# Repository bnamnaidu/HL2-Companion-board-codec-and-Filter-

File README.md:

# HL2-Companion-board-codec-and-Filter-

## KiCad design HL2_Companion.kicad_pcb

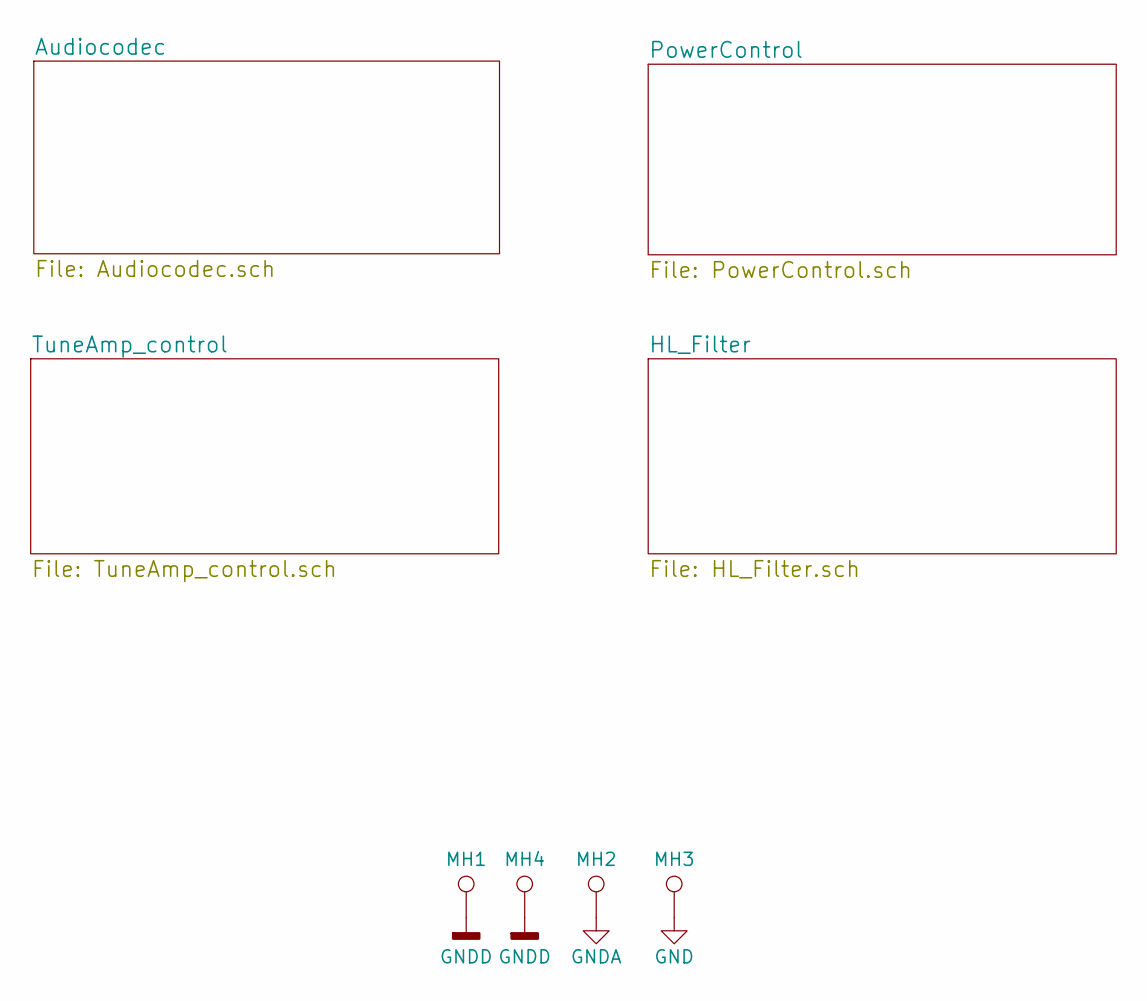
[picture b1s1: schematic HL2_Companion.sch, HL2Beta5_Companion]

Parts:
MH1, MH2, MH3, MH4: TEST_1P; m3

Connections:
GND: MH3.1; also elsewhere on the board
GNDA: MH2.1; also elsewhere on the board
GNDD: MH1.1, MH4.1; also elsewhere on the board

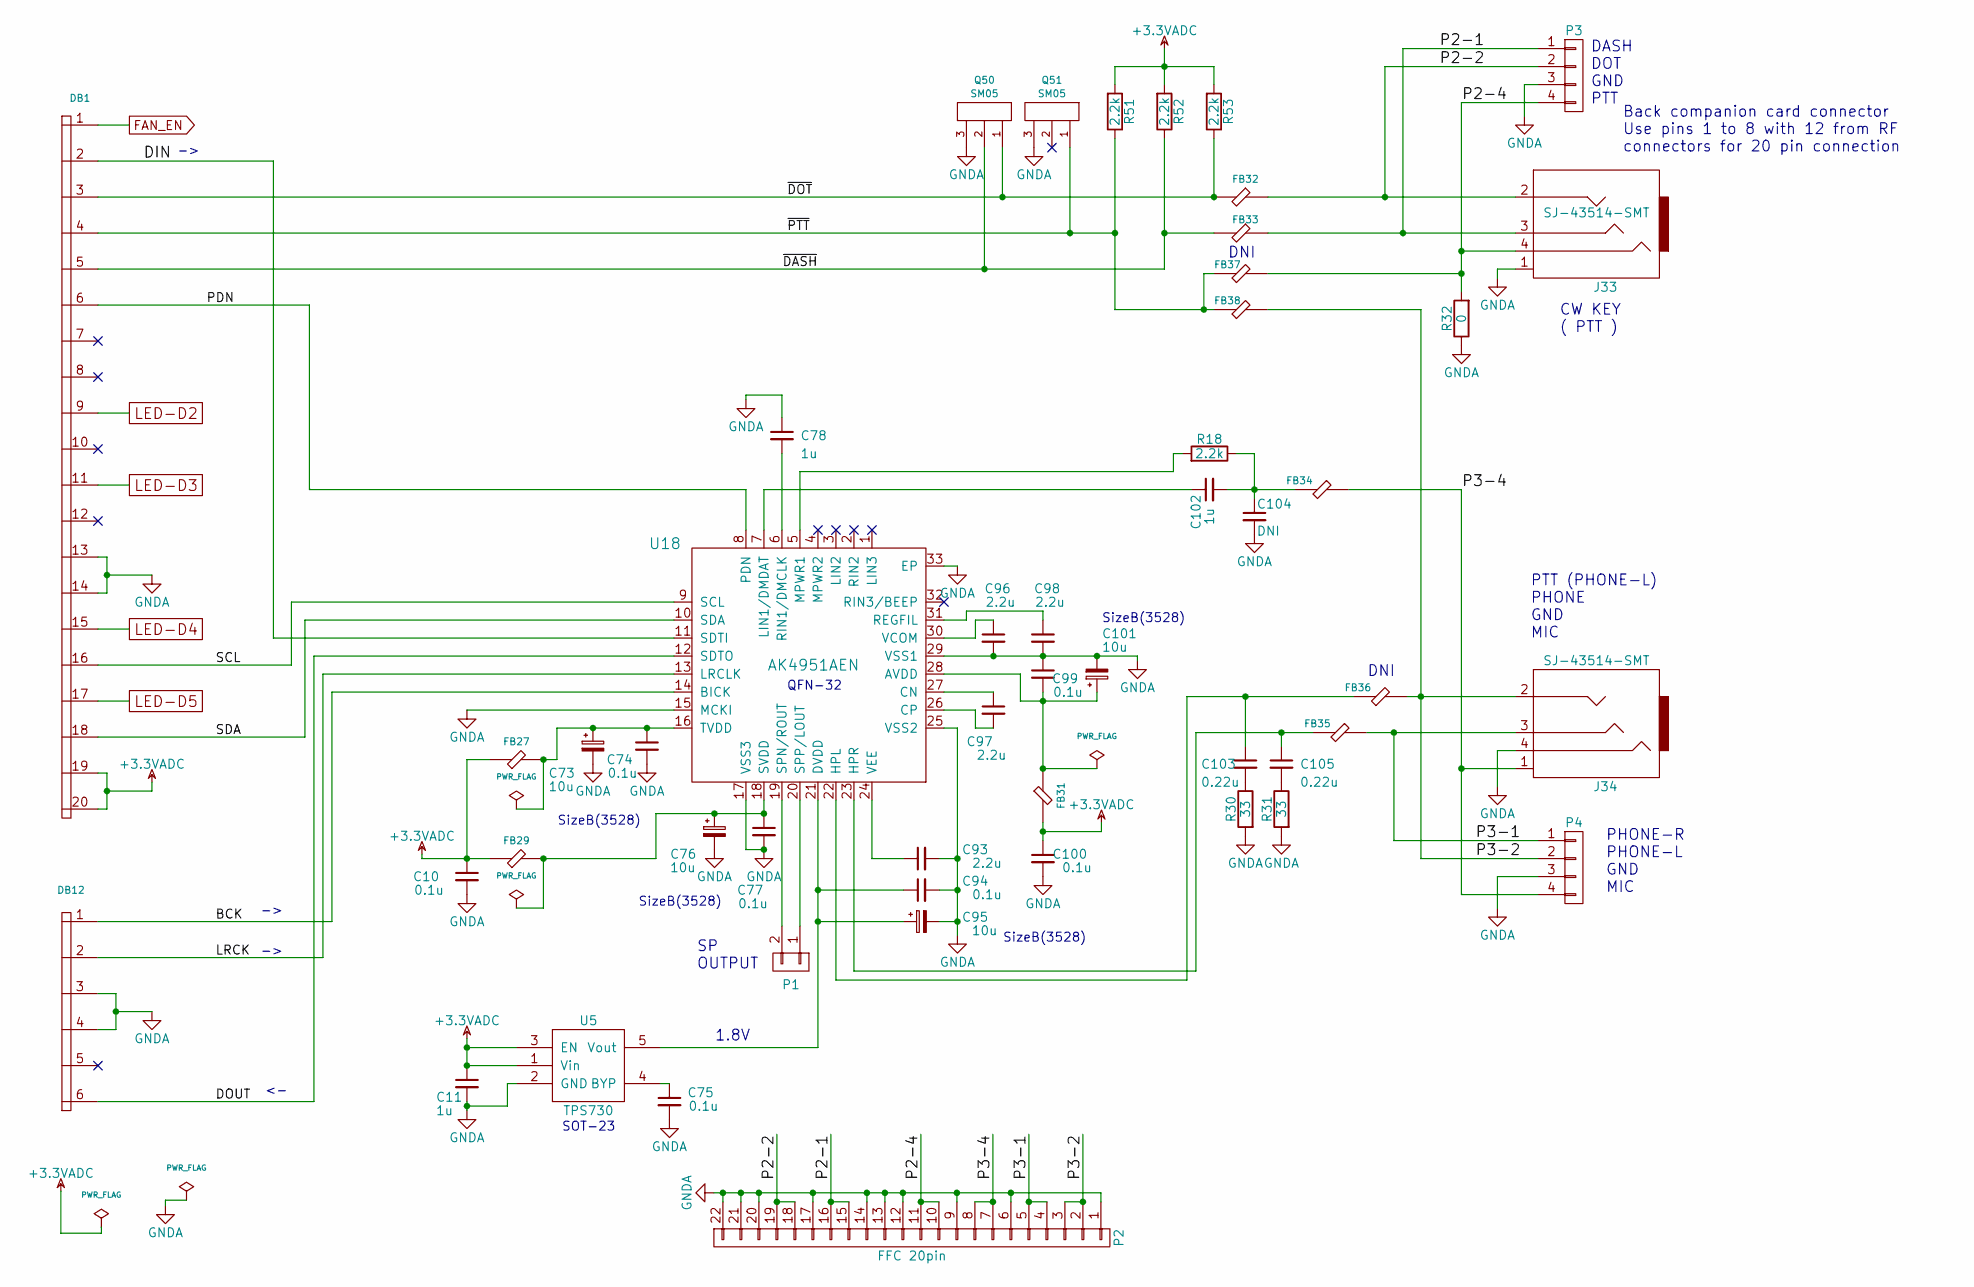
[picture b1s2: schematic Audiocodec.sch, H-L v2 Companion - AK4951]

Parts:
C10, C74, C75, C77, C94, C99, C100: 0.1u; C_0603_HandSoldering
C11, C78, C102: 1u; C_0603_HandSoldering
C73, C76, C95, C101: 10u; TantalC_SizeB_EIA-3528_Wave
C93, C96, C97, C98: 2.2u; C_0603_HandSoldering
C103, C105: 0.22u; C_0603_HandSoldering
C104: DNI; C_0603_HandSoldering
DB1: IO20; 10x2
DB12: IO6b; 3x2
FB27, FB29, FB31, FB32, FB33, FB34, FB35, FB36, FB37, FB38: FB; C_0603_HandSoldering
J33, J34: SJ-43514-SMT
P1: CONN_01X02; Pin_Header_Straight_1x02_Pitch2.54mm
P2: FFC 20pin; FFC_Kyocera_20pin
P3, P4: CONN_01X04; Pin_Header_Straight_1x04_Pitch2.54mm
Q50, Q51: SM05; SOT-23
R18, R51, R52, R53: 2.2k; C_0603_HandSoldering
R30, R31: 33; C_0603_HandSoldering
R32: 0; C_0603_HandSoldering
U5: TPS730; SOT23
U18: AK4951AEN; QFN-32-1EP_4x4mm_Pitch0.4mm_Handsoldering

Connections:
+3.3VADC: C10.1, C11.1, C100.1, DB1.19, DB1.20, FB27.2, FB29.2, FB31.1, R51.2, R52.2, R53.2, U5.1 (Vin), U5.3 (EN)
/Audiocodec/BCK: DB12.1, U18.14 (BICK)
/Audiocodec/DIN: DB1.2, U18.11 (SDTI)
/Audiocodec/DOUT: DB12.6, U18.12 (SDTO)
/Audiocodec/LRCK: DB12.2, U18.13 (LRCLK)
/Audiocodec/P2-1: FB33.2, J33.3, P2.15, P2.16, P3.1
/Audiocodec/P2-2: FB32.2, J33.2, P2.18, P2.19, P3.2
/Audiocodec/P2-4: FB37.1, J33.4, P2.10, P2.11, P3.4, R32.2
/Audiocodec/P3-1: FB35.2, J34.3, P2.4, P2.5, P4.1
/Audiocodec/P3-2: FB36.1, FB38.1, J34.2, P2.2, P2.3, P4.2
/Audiocodec/P3-4: FB34.2, J34.1, P2.7, P2.8, P4.4
/Audiocodec/PDN: DB1.6, U18.8 (PDN)
/Audiocodec/SCL: DB1.16, U18.9 (SCL)
/Audiocodec/SDA: DB1.18, U18.10 (SDA)
/Audiocodec/~DASH: DB1.5, FB33.1, Q50.2, R52.1
/Audiocodec/~DOT: DB1.3, FB32.1, Q50.1, R53.1
/Audiocodec/~PTT: DB1.4, FB37.2, FB38.2, Q51.1, R51.1
FAN_EN: DB1.1; also elsewhere on the board
GNDA: C10.2, C11.2, C73.2, C74.2, C75.2, C76.2, C77.2, C78.1, C93.2, C94.2, C95.2, C96.2, C98.2, C99.1, C100.2, C101.2, C104.2, DB1.13, DB1.14, DB12.3, DB12.4, J33.1, J34.4, P2.1, P2.6, P2.9, P2.12, P2.13, P2.14, P2.17, P2.20, P2.21, P2.22, P3.3, P4.3, Q50.3, Q51.3, R30.2, R31.2, R32.1, U5.2 (GND), U18.15 (MCKI), U18.17 (VSS3), U18.25 (VSS2), U18.29 (VSS1), U18.33 (EP); also elsewhere on the board
LED-D2: DB1.9; also elsewhere on the board
LED-D3: DB1.11; also elsewhere on the board
LED-D4: DB1.15; also elsewhere on the board
LED-D5: DB1.17; also elsewhere on the board
unnamed: C73.1, C74.1, FB27.1, U18.16 (TVDD)
unnamed: C75.1, U5.4 (BYP)
unnamed: C76.1, C77.1, FB29.1, U18.18 (SVDD)
unnamed: C78.2, U18.6 (RIN1/DMCLK)
unnamed: C93.1, U18.24 (VEE)
unnamed: C94.1, C95.1, U5.5 (Vout), U18.21 (DVDD)
unnamed: C96.1, U18.30 (VCOM)
unnamed: C97.1, U18.27 (CN)
unnamed: C97.2, U18.26 (CP)
unnamed: C98.1, U18.31 (REGFIL)
unnamed: C99.2, C101.1, FB31.2, U18.28 (AVDD)
unnamed: C102.1, U18.7 (LIN1/DMDAT)
unnamed: C102.2, C104.1, FB34.1, R18.1
unnamed: C103.1, FB36.2, U18.22 (HPL)
unnamed: C103.2, R30.1
unnamed: C105.1, FB35.1, U18.23 (HPR)
unnamed: C105.2, R31.1
unnamed: P1.1, U18.20 (SPP/LOUT)
unnamed: P1.2, U18.19 (SPN/ROUT)
unnamed: R18.2, U18.5 (MPWR1)

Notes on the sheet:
Back companion card connector Use pins 1 to 8 with 12 from RF connectors for 20 pin connection
SP OUTPUT
CW KEY ( PTT )
PTT (PHONE-L) PHONE GND MIC
1.8V
DNI
PHONE-R PHONE-L GND MIC
DASH DOT GND PTT
SizeB(3528)
SOT-23
QFN-32

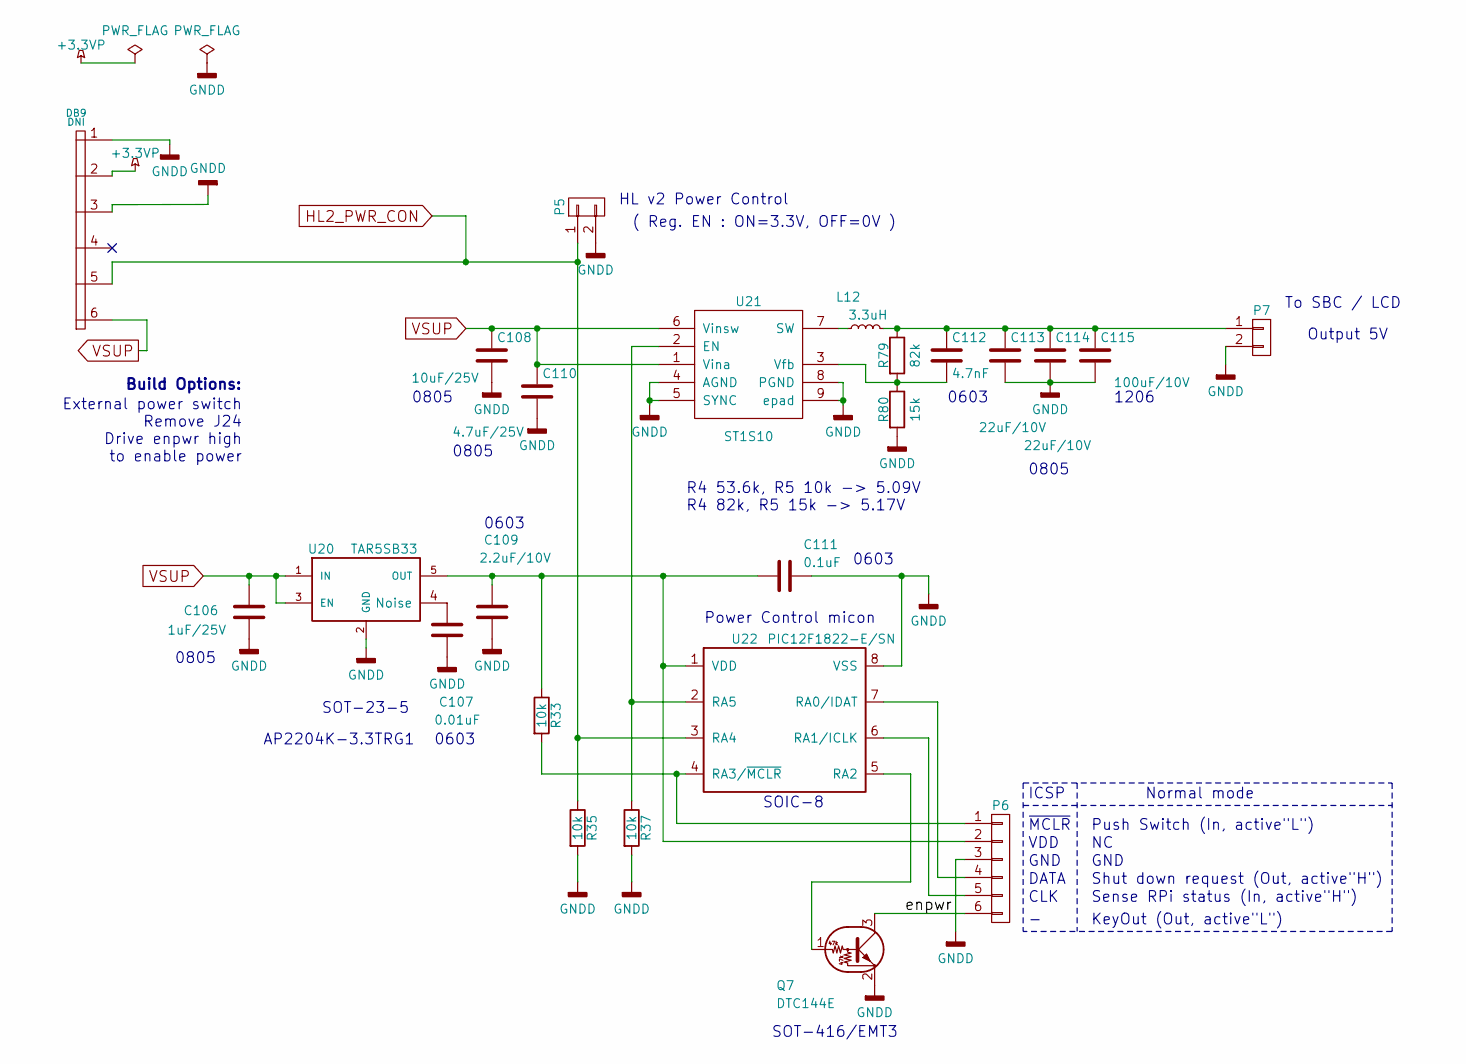
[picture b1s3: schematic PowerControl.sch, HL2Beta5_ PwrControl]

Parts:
C106: 1uF/25V; SMD-0805
C107: 0.01uF; SMD-0603
C108: 10uF/25V; SMD-0805
C109: 2.2uF/10V; SMD-0603
C110: 4.7uF/25V; SMD-0805
C111: 0.1uF; SMD-0603
C112: 4.7nF; SMD-0603
C113, C114: 22uF/10V; SMD-0805
C115: 100uF/10V; SMD-1206
DB9: IO6b; 6x1
L12: 3.3uH; GENERICPSL
P5: CONN_01X02; Pin_Header_Straight_1x02_Pitch2.54mm
P6: CONN_01X06; Pin_Header_Straight_1x06_Pitch2.54mm
P7: CONN_01X02; PINHEAD1-2
Q7: DTC144E; SOT416
R33, R35, R37: 10k; SMD-0603
R79: 82k; SMD-0603
R80: 15k; SMD-0603
U20: TAR5SB33; SOT-23-5
U21: ST1S10
U22: PIC12F1822-E/SN; SOIC-8_3.9x4.9mm_Pitch1.27mm

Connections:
+3.3VP: DB9.2; also elsewhere on the board
/PowerControl/enpwr: P6.6, Q7.3 (C)
GNDD: C106.2, C107.2, C108.2, C109.2, C110.2, C111.1, C113.2, C114.2, C115.2, DB9.1, DB9.3, P5.2, P6.3, P7.2, Q7.2 (E), R35.2, R37.2, R80.2, U20.2 (GND), U21.4 (AGND), U21.5 (SYNC), U21.8 (PGND), U21.9 (epad), U22.8 (VSS); also elsewhere on the board
HL2_PWR_CON: DB9.5, P5.1, R35.1, U22.3 (RA4); also elsewhere on the board
unnamed: C107.1, U20.4 (Noise)
unnamed: C109.1, C111.2, P6.2, R33.1, U20.5 (OUT), U22.1 (VDD)
unnamed: C112.1, C113.1, C114.1, C115.1, L12.1, P7.1, R79.1
unnamed: C112.2, R79.2, R80.1, U21.3 (Vfb)
unnamed: L12.2, U21.7 (SW)
unnamed: P6.1, R33.2, U22.4 (RA3/~MCLR)
unnamed: P6.4, U22.7 (RA0/IDAT)
unnamed: P6.5, U22.6 (RA1/ICLK)
unnamed: Q7.1 (B), U22.5 (RA2)
unnamed: R37.1, U21.2 (EN), U22.2 (RA5)
VSUP: C106.1, C108.1, C110.1, DB9.6, U20.1 (IN), U20.3 (EN), U21.1 (Vina), U21.6 (Vinsw); also elsewhere on the board

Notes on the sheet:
To SBC / LCD
ICSP
~MCLR
VDD
GND
DATA
CLK
Shut down request (Out, active"H")
Sense RPi status (In, active"H")
Output 5V
Normal mode
Push Switch (In, active"L")
HL v2 Power Control
( Reg. EN : ON=3.3V, OFF=0V )
Power Control micon
SOT-23-5
SOIC-8
0805
1206
0603
SOT-416/EMT3
R4 53.6k, R5 10k -> 5.09V R4 82k, R5 15k -> 5.17V
AP2204K-3.3TRG1
KeyOut (Out, active"L")
Build Options:
External power switch Remove J24 Drive enpwr high to enable power

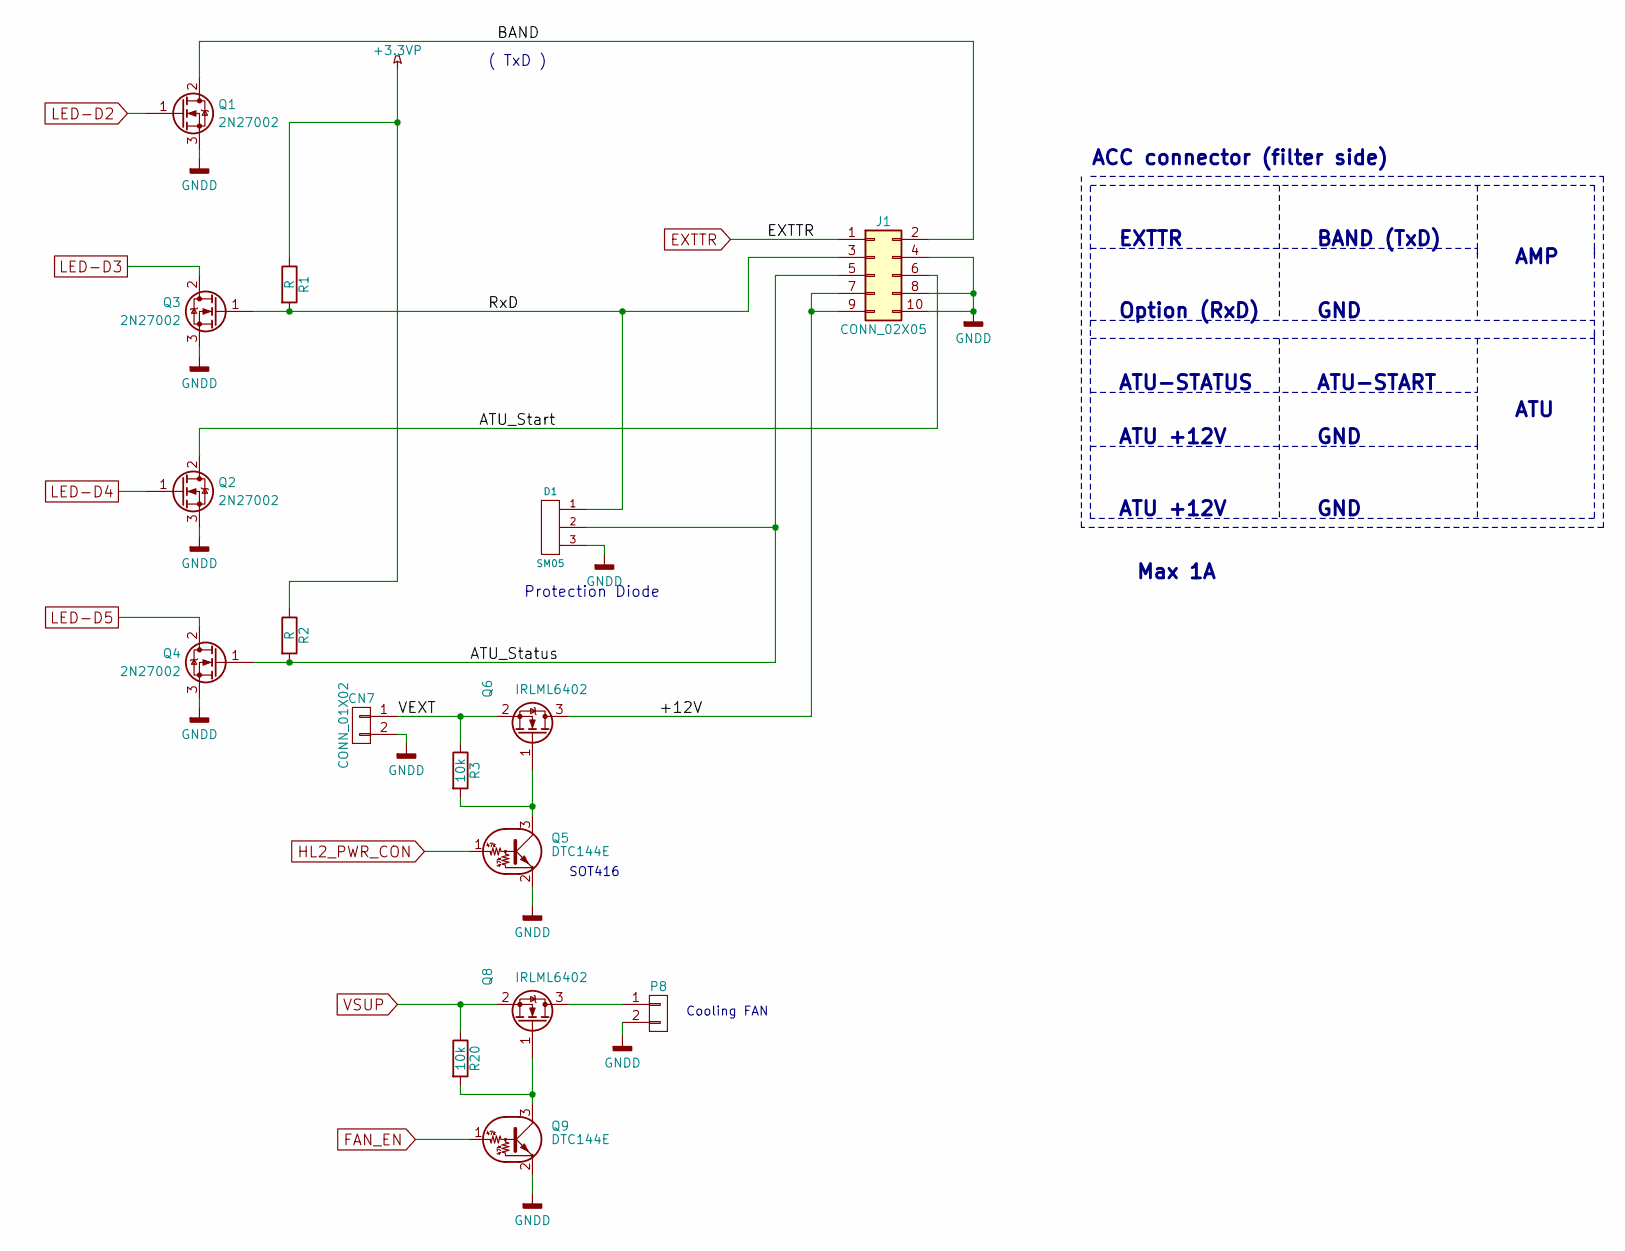
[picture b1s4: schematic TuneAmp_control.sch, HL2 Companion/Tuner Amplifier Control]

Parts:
CN7: CONN_01X02; CN7
D1: SM05; SOT-23
J1: CONN_02X05; 5x2
P8: CONN_01X02; PINHEAD1-2
Q1, Q2, Q3, Q4: 2N27002; SOT-23
Q5, Q9: DTC144E; SOT416
Q6, Q8: IRLML6402; SOT23_3
R1, R2: R; C_0603_HandSoldering
R3, R20: 10k; C_0603_HandSoldering

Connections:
+3.3VP: R1.1, R2.1; also elsewhere on the board
/TuneAmp_control/+12V: J1.7, J1.9, Q6.3 (D)
/TuneAmp_control/ATU_Start: J1.6, Q2.2 (D)
/TuneAmp_control/ATU_Status: D1.2, J1.5, Q4.1 (G), R2.2
/TuneAmp_control/BAND: J1.2, Q1.2 (D)
/TuneAmp_control/RxD: D1.1, J1.3, Q3.1 (G), R1.2
/TuneAmp_control/VEXT: CN7.1, Q6.2 (S), R3.1
EXTTR: J1.1; also elsewhere on the board
FAN_EN: Q9.1 (B); also elsewhere on the board
GNDD: CN7.2, D1.3, J1.4, J1.8, J1.10, P8.2, Q1.3 (S), Q2.3 (S), Q3.3 (S), Q4.3 (S), Q5.2 (E), Q9.2 (E); also elsewhere on the board
HL2_PWR_CON: Q5.1 (B); also elsewhere on the board
LED-D2: Q1.1 (G); also elsewhere on the board
LED-D3: Q3.2 (D); also elsewhere on the board
LED-D4: Q2.1 (G); also elsewhere on the board
LED-D5: Q4.2 (D); also elsewhere on the board
unnamed: P8.1, Q8.3 (D)
unnamed: Q5.3 (C), Q6.1 (G), R3.2
unnamed: Q8.1 (G), Q9.3 (C), R20.2
VSUP: Q8.2 (S), R20.1; also elsewhere on the board

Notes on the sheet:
( TxD )
Protection Diode
EXTTR
BAND (TxD)
Option (RxD)
GND
AMP
ATU-STATUS
ATU-START
ATU +12V
ATU
Max 1A
ACC connector (filter side)
SOT416
Cooling FAN

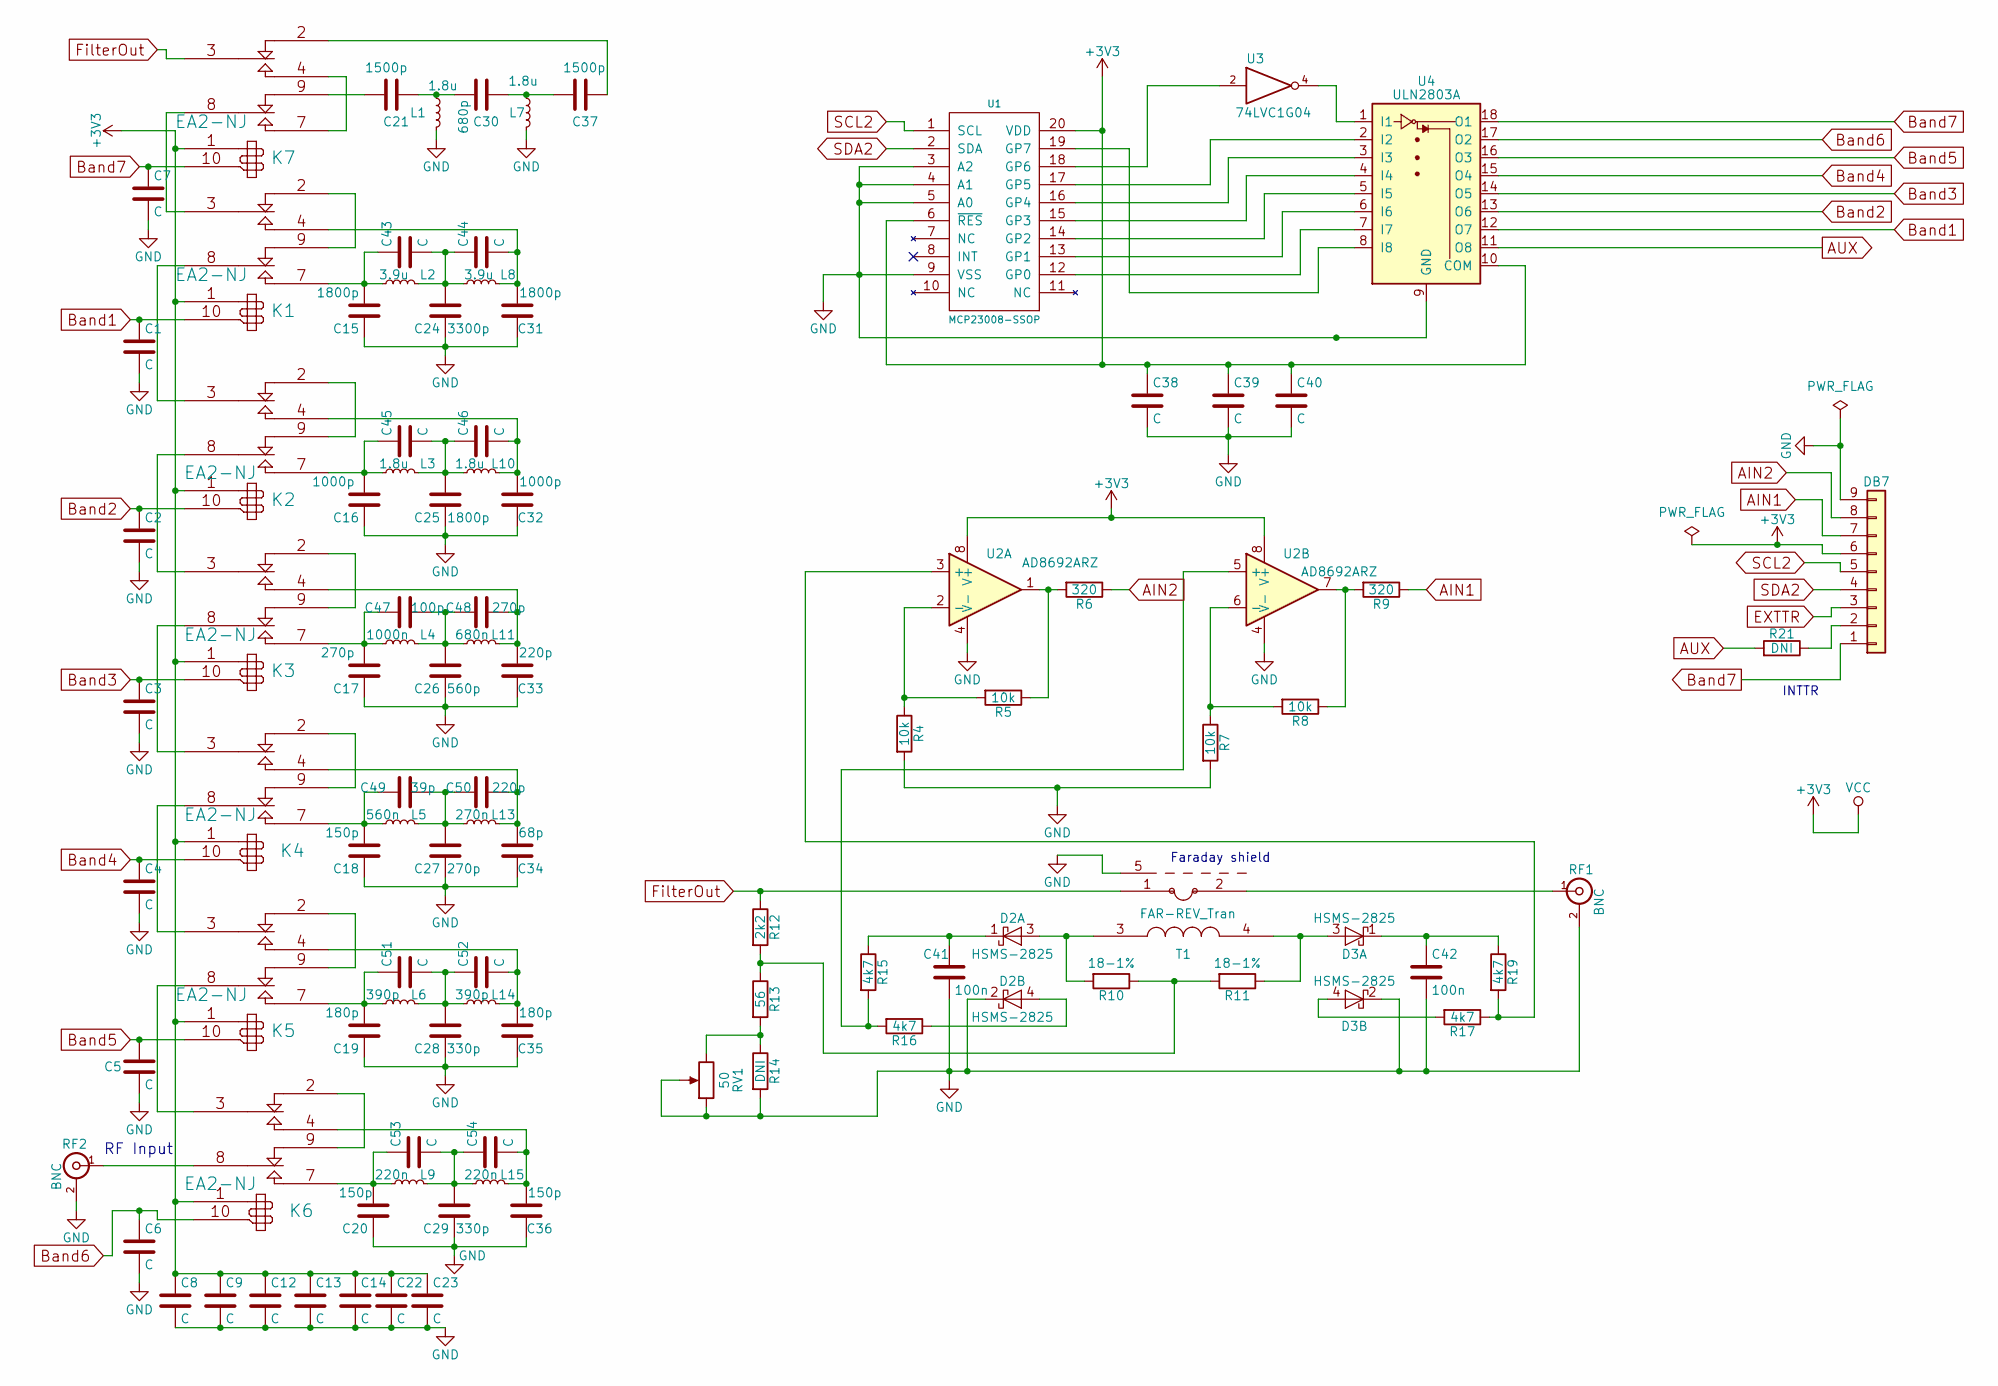
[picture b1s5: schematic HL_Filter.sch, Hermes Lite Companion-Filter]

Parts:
C1, C2, C3, C4, C5, C6, C7, C8, C9, C12, C13, C14, C22, C23, C38, C39, C40, C43, C44, C45, C46, C51, C52, C53, C54: C; C_0805_HandSoldering
C15, C25, C31: 1800p; C_0805_HandSoldering
C16, C32: 1000p; C_0805_HandSoldering
C17, C27, C48: 270p; C_0805_HandSoldering
C18, C20, C36: 150p; C_0805_HandSoldering
C19, C35: 180p; C_0805_HandSoldering
C21, C37: 1500p; C_0805_HandSoldering
C24: 3300p; C_0805_HandSoldering
C26: 560p; C_0805_HandSoldering
C28, C29: 330p; C_0805_HandSoldering
C30: 680p; C_0805_HandSoldering
C33, C50: 220p; C_0805_HandSoldering
C34: 68p; C_0805_HandSoldering
C41, C42: 100n; C_0805_HandSoldering
C47: 100p; C_0805_HandSoldering
C49: 39p; C_0805_HandSoldering
D2, D3: HSMS-2825; SOT-143
DB7: IO9; 9x1
K1, K2, K3, K4, K5, K6, K7: EA2-NJ; Relay_EA2
L1, L3, L7, L10: 1.8u; Toroid_Horizontal-T30
L2, L8: 3.9u; Toroid_Horizontal-T30
L4: 1000n; Toroid_Horizontal-T30
L5: 560n; Toroid_Horizontal-T30
L6, L14: 390p; Toroid_Horizontal-T30
L9, L15: 220n; Toroid_Horizontal-T30
L11: 680n; Toroid_Horizontal-T30
L13: 270n; Toroid_Horizontal-T30
R4, R5, R7, R8: 10k; R_0805_HandSoldering
R6, R9: 320; R_0805_HandSoldering
R10, R11: 18-1%; R_0805_HandSoldering
R12: 2k2; R_0805_HandSoldering
R13: 56; R_0805_HandSoldering
R14, R21: DNI; R_0805_HandSoldering
R15, R16, R17, R19: 4k7; R_0805_HandSoldering
RF1, RF2: BNC; SMAEDGE_TH_R
RV1: 50; Potentiometer_Trimmer-EVM3E
T1: FAR-REV_Tran
U1: MCP23008-SSOP; SOIC-20W_7.5x12.8mm_Pitch1.27mm
U2: AD8692ARZ; SO-8_5.3x6.2mm_Pitch1.27mm
U3: 74LVC1G04; SOT-353_SC-70-5_Handsoldering
U4: ULN2803A; SOIC-18W_7.5x11.6mm_Pitch1.27mm

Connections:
+3V3: C8.1, C9.1, C12.1, C13.1, C14.1, C22.1, C23.1, C38.1, C39.1, C40.1, DB7.6, K1.1, K2.1, K3.1, K4.1, K5.1, K6.1, K7.1, U1.6 (~RES), U1.20 (VDD), U2.8 (V+), U3.5 (VCC), U4.10 (COM)
AIN1: DB7.7, R9.1
AIN2: DB7.8, R6.1
AUX: R21.2, U4.11 (O8)
Band1: C1.1, K1.10, U4.12 (O7)
Band2: C2.1, K2.10, U4.13 (O6)
Band3: C3.1, K3.10, U4.14 (O5)
Band4: C4.1, K4.10, U4.15 (O4)
Band5: C5.1, K5.10, U4.16 (O3)
Band6: C6.1, K6.10, U4.17 (O2)
Band7: C7.1, DB7.1, K7.10, U4.18 (O1)
EXTTR: DB7.3; also elsewhere on the board
FilterOut: K7.3 (C2), R12.1, T1.1 (PR2)
GND: C1.2, C2.2, C3.2, C4.2, C5.2, C6.2, C7.2, C8.2, C9.2, C12.2, C13.2, C14.2, C15.1, C16.1, C17.1, C18.1, C19.1, C20.1, C22.2, C23.2, C24.1, C25.1, C26.1, C27.1, C28.1, C29.1, C31.1, C32.1, C33.1, C34.1, C35.1, C36.1, C38.2, C39.2, C40.2, C41.2, C42.2, D2.2 (K), D3.2 (K), DB7.9, L1.2, L7.2, R4.2, R7.2, R14.2, RF1.2 (Ext), RF2.2 (Ext), RV1.1, RV1.2, T1.5 (GND), U1.3 (A2), U1.4 (A1), U1.5 (A0), U1.9 (VSS), U2.4 (V-), U3.3 (GND), U4.9 (GND); also elsewhere on the board
unnamed: C15.2, C43.1, K1.7 (T1), L2.2
unnamed: C16.2, C45.1, K2.7 (T1), L3.2
unnamed: C17.2, C47.1, K3.7 (T1), L4.2
unnamed: C18.2, C49.1, K4.7 (T1), L5.2
unnamed: C19.2, C51.1, K5.7 (T1), L6.2
unnamed: C20.2, C53.1, K6.7 (T1), L9.2
unnamed: C21.1, C30.2, L1.1
unnamed: C21.2, K7.9 (R1)
unnamed: C24.2, C43.2, C44.1, L2.1, L8.1
unnamed: C25.2, C45.2, C46.1, L3.1, L10.1
unnamed: C26.2, C47.2, C48.1, L4.1, L11.1
unnamed: C27.2, C49.2, C50.1, L5.1, L13.1
unnamed: C28.2, C51.2, C52.1, L6.1, L14.1
unnamed: C29.2, C53.2, C54.1, L9.1, L15.1
unnamed: C30.1, C37.2, L7.1
unnamed: C31.2, C44.2, K1.4 (T2), L8.2
unnamed: C32.2, C46.2, K2.4 (T2), L10.2
unnamed: C33.2, C48.2, K3.4 (T2), L11.2
unnamed: C34.2, C50.2, K4.4 (T2), L13.2
unnamed: C35.2, C52.2, K5.4 (T2), L14.2
unnamed: C36.2, C54.2, K6.4 (T2), L15.2
unnamed: C37.1, K7.2 (R2)
unnamed: C41.1, D2.1 (K), R15.1
unnamed: C42.1, D3.1 (K), R19.1
unnamed: D2.3 (A), R10.2, T1.3 (S1)
unnamed: D2.4 (A), R16.1
unnamed: D3.3 (A), R11.1, T1.4 (S2)
unnamed: D3.4 (A), R17.2
unnamed: DB7.2, R21.1
unnamed: K1.2 (R2), K1.9 (R1)
unnamed: K1.3 (C2), K7.8 (C1)
unnamed: K1.8 (C1), K2.3 (C2)
unnamed: K2.2 (R2), K2.9 (R1)
unnamed: K2.8 (C1), K3.3 (C2)
unnamed: K3.2 (R2), K3.9 (R1)
unnamed: K3.8 (C1), K4.3 (C2)
unnamed: K4.2 (R2), K4.9 (R1)
unnamed: K4.8 (C1), K5.3 (C2)
unnamed: K5.2 (R2), K5.9 (R1)
unnamed: K5.8 (C1), K6.3 (C2)
unnamed: K6.2 (R2), K6.9 (R1)
unnamed: K6.8 (C1), RF2.1 (In)
unnamed: K7.4 (T2), K7.7 (T1)
unnamed: R4.1, R5.2, U2.2 (-)
unnamed: R5.1, R6.2, U2.1
unnamed: R7.1, R8.2, U2.6 (-)
unnamed: R8.1, R9.2, U2.7
unnamed: R10.1, R11.2, R12.2, R13.1
unnamed: R13.2, R14.1, RV1.3
unnamed: R15.2, R16.2, U2.5 (+)
unnamed: R17.1, R19.2, U2.3 (+)
unnamed: RF1.1 (In), T1.2 (PR1)
unnamed: U1.12 (GP0), U4.7 (I7)
unnamed: U1.13 (GP1), U4.6 (I6)
unnamed: U1.14 (GP2), U4.5 (I5)
unnamed: U1.15 (GP3), U4.4 (I4)
unnamed: U1.16 (GP4), U4.3 (I3)
unnamed: U1.17 (GP5), U4.2 (I2)
unnamed: U1.18 (GP6), U3.2
unnamed: U1.19 (GP7), U4.8 (I8)
unnamed: U3.4, U4.1 (I1)
SCL2: DB7.5, U1.1 (SCL)
SDA2: DB7.4, U1.2 (SDA)

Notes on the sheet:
RF Input
Faraday shield
INTTR

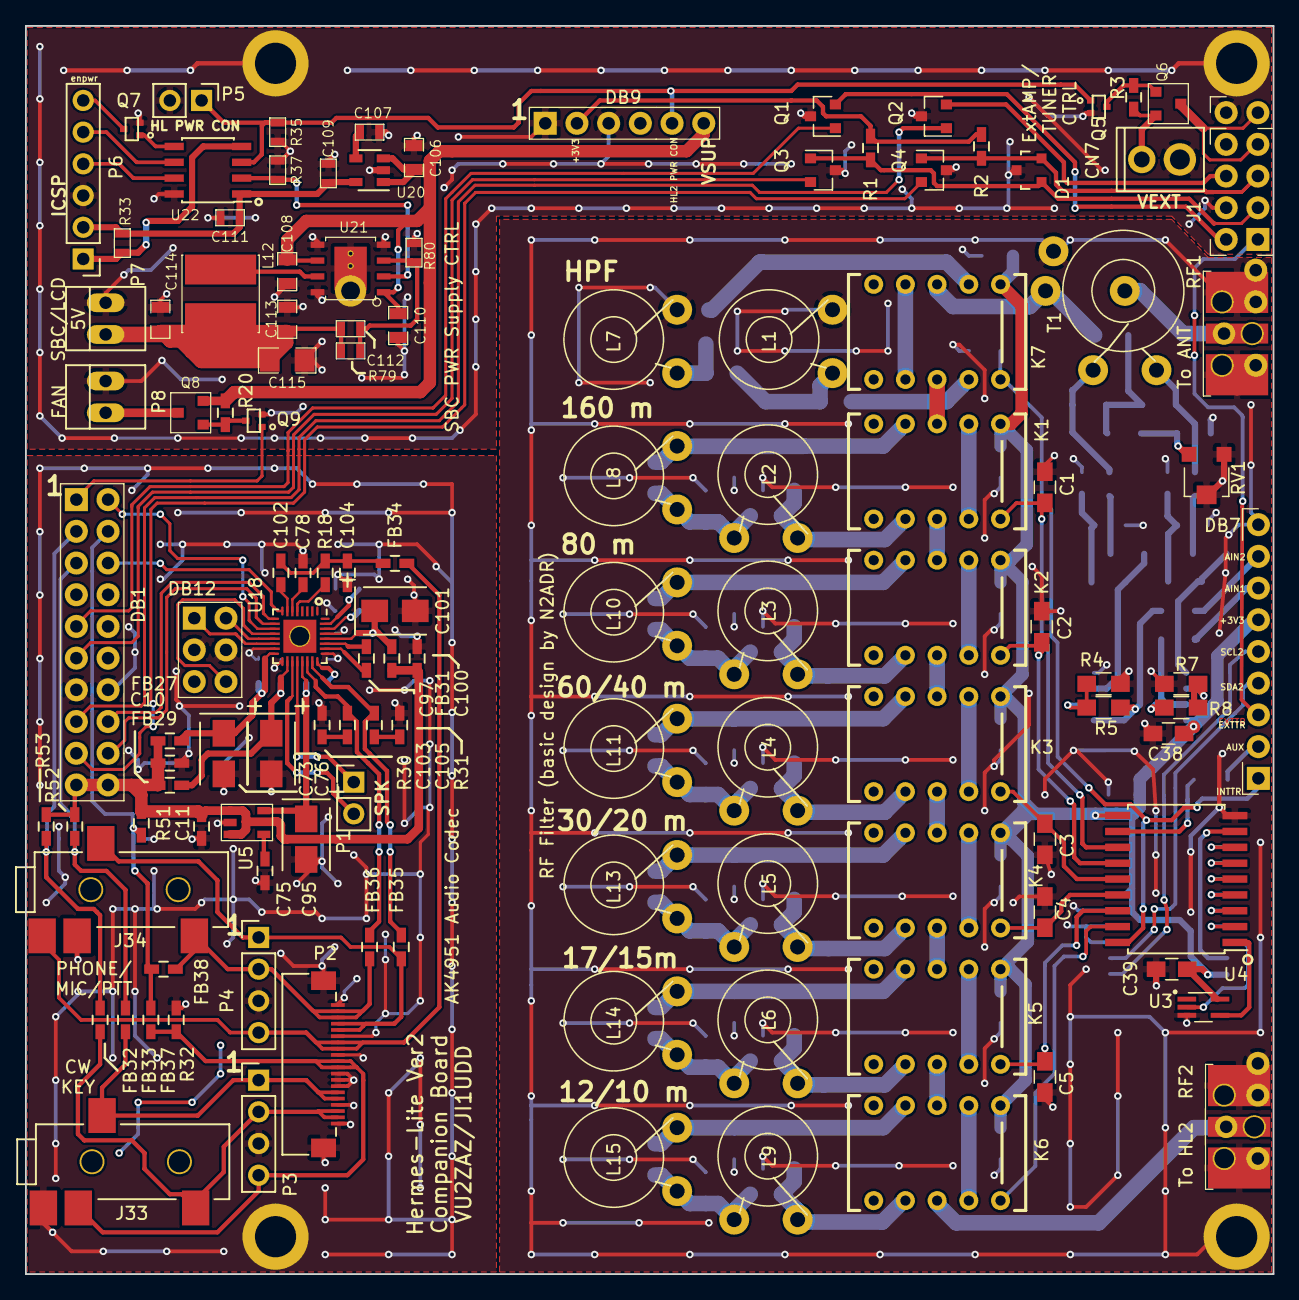
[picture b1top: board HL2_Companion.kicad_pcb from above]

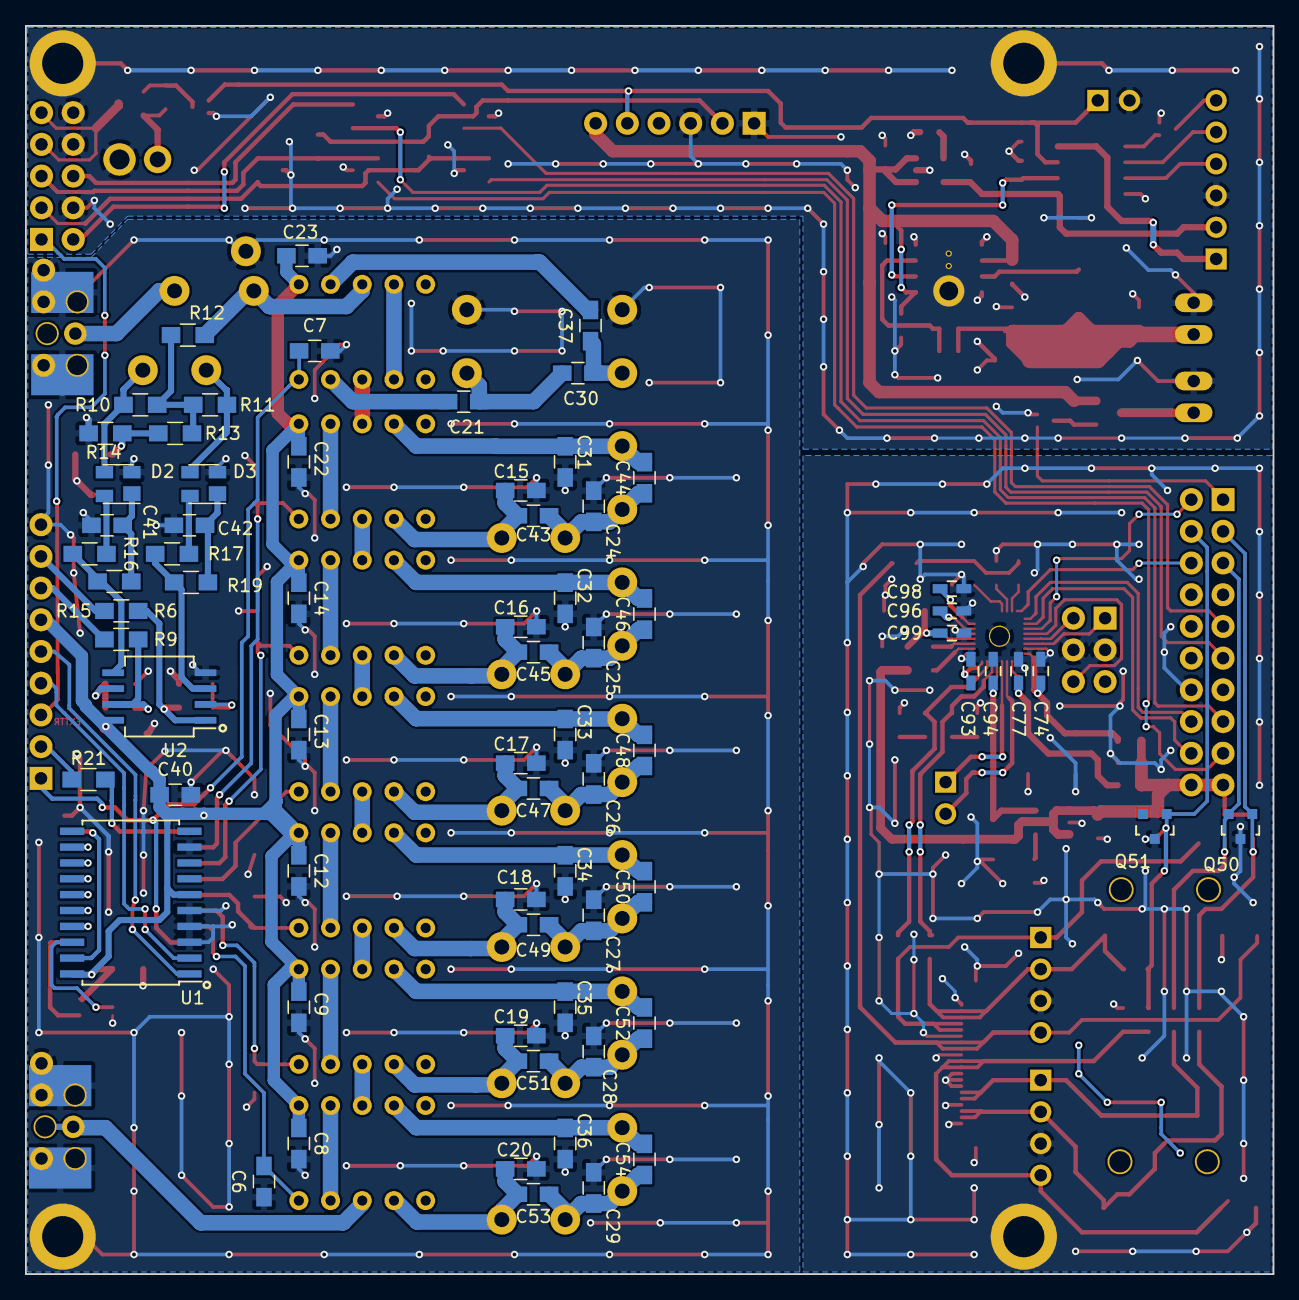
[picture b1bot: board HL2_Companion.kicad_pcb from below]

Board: 2 copper layers, 99.9 x 100.0 mm, 194 parts (70 on the bottom side), 144 nets.

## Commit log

2018-02-07 2nd commit
2018-02-07 Revert "Initial commit"
    This reverts commit 31c3f8e4b0acd1de52ab9e73223d57302cca0596.
2018-02-07 Revert "2nd commit"
    This reverts commit c2c8c64dbba293bd2cada59ce21b839a84bcafa0.
2018-02-07 Revert "Revert "2nd commit""
    This reverts commit edb932220130fd3fafe1bb85e67b4344efccf7b3.
2018-02-07 deleted files
2018-02-07 deletd
2018-02-07 modified
2018-02-08 gerber corrected
2018-02-08 gerber modified
